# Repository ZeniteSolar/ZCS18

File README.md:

# ZCS18 - Zênite CAN! Shield 2018
The piece of hardware used in almost all modules in the boat of Zênite Solar Team on 2018.

## About

![zenite_logo] 

[Zênite Solar TEAM](https://github.com/ZeniteSolar) is an universitary project from [IFSC](http://www.ifsc.edu.br) focused on the development of a high performance solar boat for races and it aims to be completly open source.

- All the hardware was developed using [KiCad](http://kicad-pcb.org/);
- Simulations was done using [LTSpice](http://www.analog.com/en/design-center/design-tools-and-calculators/ltspice-simulator.html);
- Schematics are available [here][Schematic];
- BOM are available [here][BOM];

## Status

- [x] Simulations
- [x] Schematics
- [x] PCB
- [x] Fabrication
- [ ] Assembly
- [ ] Test
- [ ] Basic Firmware for reference

## Board View

![kicad3d_front_populated] 

***

[Schematic]: PDF/atmega_can_shield.pdf "Schematics"
[BOM]: PDF/BOM.pdf "Bill Of Materials"
[photo_front]: IMG/front.PNG "Fabricated Front"
[photo_back]: IMG/front.PNG "Fabricated Back"
[photo_front]: IMG/front.PNG "Populated Front"
[photo_back]: IMG/front.PNG "Populated Back"
[kicad3d_front]: IMG/front.PNG "Kicad Front"
[kicad3d_back]: IMG/back.PNG "Kicad Back"
[kicad3d_front_populated]: IMG/front_populated.PNG "Kicad Populated Front"
[kicad3d_back_populated]: IMG/back_populated.PNG "Kicad Populated Back"
[kicad3d_populated_angled]: IMG/populated_angled.PNG "Kicad Populated Board 3D View"
[zenite_logo]: https://avatars2.githubusercontent.com/u/8411347?s=100 "Zênite Solar Team Logo"

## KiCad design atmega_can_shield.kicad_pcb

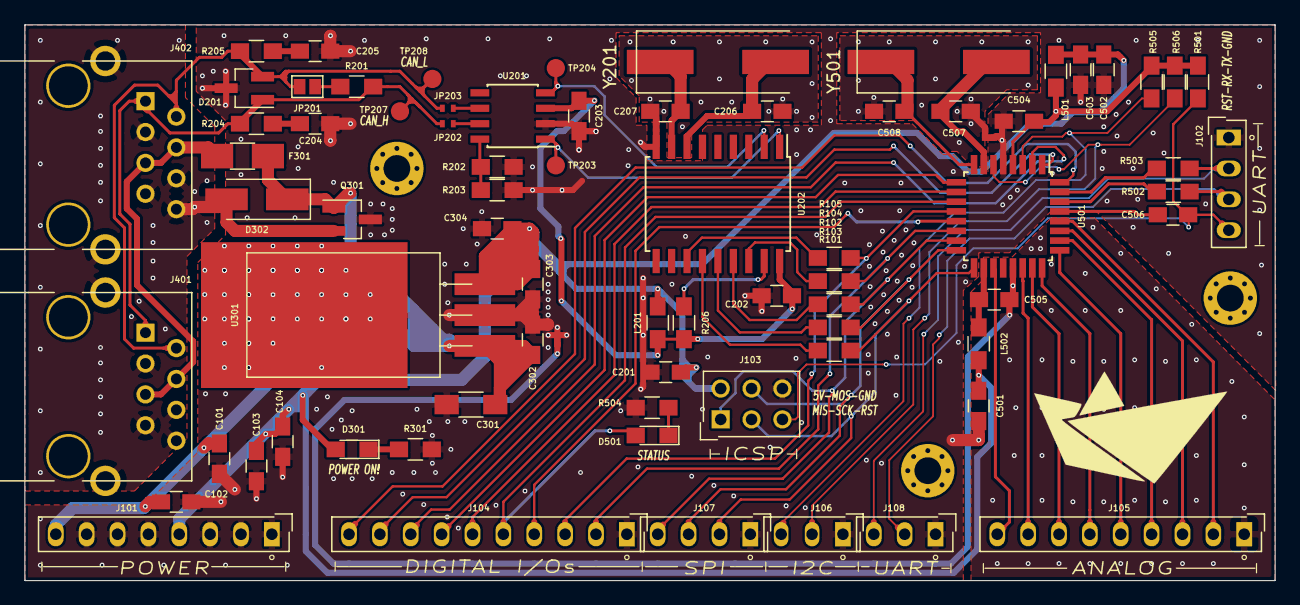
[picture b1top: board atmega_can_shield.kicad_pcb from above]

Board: 2 copper layers, 102.9 x 45.7 mm, 79 parts (0 on the bottom side), 60 nets.

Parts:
C101, C103, C503: 1u; C_0805_HandSoldering
C102, C104: 100n; C_0805_HandSoldering
C201, C202, C203, C302, C303, C501, C502, C504, C505, C506: 100nF; C_0805_HandSoldering
C204, C205: 560p; C_0805_HandSoldering
C206, C207, C507, C508: 22pF; C_0805_HandSoldering
C301: 10uF; C_1206_HandSoldering
C304: 1uF; C_0805_HandSoldering
D201: pesd1can; SOT-23_Handsoldering
D301, D501: LED_RED; LED_0805_HandSoldering
D302: TVS 24V 400W; D_SMA_Handsoldering
F301: 500mA resettable; Fuse_SMD1206_HandSoldering
J101: SUPPLY; SL-108-X-XX_1x08
J102: USART; SL-104-X-XX_1x04
J103: ICSP; SDL-106-X-XX_2x03
J104: DIGITAL I/Os; SL-110-X-XX_1x10
J105: ANALOG; SL-109-X-XX_1x09
J106: I2C; SL-103-X-XX_1x03
J107: SPI; SL-104-X-XX_1x04
J108: USART; SL-103-X-XX_1x03
J201, J301, J501: NetTie; µNetTie-I_Connected_SMD
J401, J402: RJ45; RJ45_YH59_01
JP201: Termination; GS2
JP202, JP203: Jumper_2_Open; R_0402_NoSilk
L201, L501, L502: 10uH; L_0805_HandSoldering
MK101, MK102, MK103: Mounting_Hole; MountingHole_2.2mm_M2_Pad_Via
Q301: si2308cds; SOT-23_Handsoldering
R101, R102, R103, R104, R105, R204, R205: 100; R_0805_HandSoldering
R201: 120; R_0805_HandSoldering
R202, R203, R206, R301, R501, R504, R505, R506: 10k; R_0805_HandSoldering
R502, R503: 1k; R_0805_HandSoldering
TP203: TXCAN; Measurement_Point_Round-SMD-Pad_Small
TP204: RXCAN; Measurement_Point_Round-SMD-Pad_Small
TP207: CAN_H; Measurement_Point_Round-SMD-Pad_Small
TP208: CAN_L; Measurement_Point_Round-SMD-Pad_Small
U201: MCP2551-I/SN; SOIC-8_3.9x4.9mm_Pitch1.27mm
U202: MCP2515-E/ST-SOIC18; SOIC-18W_7.5x11.6mm_Pitch1.27mm
U301: LM7805; TO-220_Horizontal_SMD
U501: ATMEGA328P-AU_alt; TQFP-32_7x7mm_Pitch0.8mm
Y201, Y501: 16MHz; Crystal_SMD_HC49_4HSMX

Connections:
+5V: C103.2, C104.1, C201.2, C303.1, C304.1, C501.1, C502.1, C503.2, D301.2, J101.4, J103.2, L201.2, L501.2, L502.2, U301.3
+5VA: C505.2, L502.1, U501.18
+5VD: C504.2, L501.1, R501.1, R505.1, R506.1, U501.4
+18V: C101.2, C102.1, C301.1, C302.1, D302.1, F301.2, J101.8, Q301.1, U301.1
/CANBUS CONN/CAN_GND: D302.2, J401.3, J401.6, J401.7, J401.8, J401.9, J402.3, J402.6, J402.7, J402.8, J402.9, Q301.2
/CANBUS CONN/CAN_H: D201.1, J401.1, J402.1, JP202.2, R201.2, R204.1, TP207.1
/CANBUS CONN/CAN_L: D201.2, J401.2, J402.2, JP201.2, JP203.2, R205.1, TP208.1
/CANBUS/CLK_N: C207.1, U202.8, Y201.1
/CANBUS/CLK_P: C206.2, U202.7, Y201.2
/CANBUS/CS: R104.1, U202.16
/CANBUS/INT: R105.1, U202.12
/CANBUS/RXCAN: TP204.1, U201.4, U202.2
/CANBUS/SCK: R101.1, U202.13
/CANBUS/SI: R103.1, U202.14
/CANBUS/SO: R102.1, U202.15
/CANBUS/TXCAN: TP203.1, U201.1, U202.1
/CANBUS/local_VCC: C202.2, C203.2, L201.1, R206.1, U201.3, U202.18
/MCU/ADC0: J105.7, U501.23
/MCU/ADC1: J105.6, U501.24
/MCU/ADC2: J105.5, U501.25
/MCU/ADC3: J105.4, U501.26
/MCU/ADC4: J105.3, U501.27
/MCU/ADC5: J105.2, U501.28
/MCU/ADC6: J105.9, U501.19
/MCU/ADC7: J105.8, U501.22
/MCU/CLK_N: C508.1, U501.8, Y501.1
/MCU/CLK_P: C507.1, U501.7, Y501.2
/MCU/MCP_INT: J104.3, R105.2, U501.12
/MCU/PB1: J104.4, U501.13
/MCU/PD2: J104.10, U501.32
/MCU/PD3: J104.9, U501.1
/MCU/PD4: J104.8, U501.2
/MCU/PD5: J104.7, U501.9
/MCU/PD6: J104.6, U501.10
/MCU/PD7: D501.2, J104.5, U501.11
/MCU/RST: C506.2, U501.29
/MCU/RX: R502.1, U501.30
/MCU/SCL1: J106.2, R506.2, U501.6
/MCU/SDA1: J106.3, R505.2, U501.3
/MCU/SPI_SS: J104.2, R104.2, U501.14
/MCU/TX: R503.1, U501.31
/MISO: J103.1, J107.4, R102.2, U501.15
/MOSI: J103.4, J107.3, R103.2, U501.16
/POWER SUPPLY/+18V_IN: F301.1, J401.4, J401.5, J402.4, J402.5
/RESET: C506.1, J102.4, J103.5, R501.2
/RX: J102.3, J108.2, R502.2
/SCK: J103.3, J107.2, R101.2, U501.17
/TX: J102.2, J108.3, R503.2
GND: C101.1, C102.2, C103.1, C104.2, C201.1, C202.1, C203.1, C204.1, C205.1, C301.2, C302.2, C303.2, C304.2, C501.2, C502.2, C503.1, C504.1, D201.3, J101.1, J101.2, J101.3, J101.5, J101.6, J101.7, J102.1, J103.6, J104.1, J106.1, J107.1, J108.1, J201.2, J301.1, J501.2, Q301.3, R202.2, R203.2, R301.2, R504.2, U201.2, U202.9, U301.2, U501.5
GNDA: C505.1, J105.1, J301.2, U501.21
GNDD: C206.1, C207.2, C507.2, C508.2, J201.1, J501.1
unnamed: C204.2, R204.2
unnamed: C205.2, R205.2
unnamed: D301.1, R301.1
unnamed: D501.1, R504.1
unnamed: JP201.1, R201.1
unnamed: JP202.1, U201.7
unnamed: JP203.1, U201.6
unnamed: R202.1, R203.1, U201.8
unnamed: R206.2, U202.17

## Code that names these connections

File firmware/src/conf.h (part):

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#define     BatOverVoltageInterrupt_PORT PORTD
#define     BatOverVoltageInterrupt_PIN  PIND
#define     BatOverVoltageInterrupt_DDR  DDRD
#define     BatOverVoltageInterrupt      PD2
#endif // ENABLE_HARDWARE_OVERVOLTAGE_INTERRUPT

#ifdef ENABLE_HARDWARE_ENABLE_SWITCH_INTERRUPT
#define     Enable_PORT             PORTD
#define     Enable_PIN              PIND
#define     Enable_DDR              DDRD
#define     Enable                  PD3
#endif // ENABLE_HARDWARE_ENABLE_SWITCH_INTERRUPT


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#define     PWM_PORT                PORTB
#define     PWM_PIN                 PINB
#define     PWM_DDR                 DDRB
#define     PWM                     PB1
#endif // PWM_ON

#ifdef LED_ON
#define     LED_PORT                PORTD
#define     LED_PIN                 PIND
#define     LED_DDR                 DDRD
#define     LED                     PD7
#define     cpl_led()               cpl_bit(LED_PORT, LED)
#define     set_led()               set_bit(LED_PORT, LED)
#define     clr_led()               clr_bit(LED_PORT, LED)
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
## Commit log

2018-05-26 First commit: the project was finished and mmanufactured (just the pcbs) but not tested nor documented yet.
2018-05-29 Changed 3D to KiCAD 5 and exported .wrl file
2018-05-29 PCB material changed to black on .wrl file.
2018-05-29 .step files changed to .wrl
2018-05-29 images was missing .PNG
2018-07-18 initial firmware copied from MCC17, small changes to compile and upload for 328pb
2018-07-18 changed MISO and MOSI using software serial
2018-07-18 added pragma messages for included modules
2018-07-20 Chaned to compile atmega328pb
2018-07-20 unecessary file.
2018-07-20 SILENCE enabled
2018-07-20 modules interdependency fixed
2018-07-20 gitignore updated
2018-07-20 Status led changed to new pin and added a blink pattern to main loop if MACHINE_ON isnt defined.
2018-07-20 ADC setted to 5kHz, some other minor improvements.
2018-07-20 Comments added
2018-07-20 USART, WATCHDOG, PWM, ADC working. Now testing machine
2018-07-20 ADC readings tested, ifdefs 8bits fixed
2018-07-20 ADC tested: OK. Reading 1021 at 5V, 0 at 0V
2018-07-22 PWM changed to mode 14 to get better resolution for 100kHz.
2018-07-22 code organization
2018-07-22 added a print version for 32 bits unsigned
2018-07-30 Added precompiled PWM configurations. Tested -> OK
2018-08-22 wdt time changed to 4 seconds because 2 wasn't fine
2018-08-22 This is almost the firmware for MCC module
2018-08-24 testing...
2018-08-24 adc_data_ready changed to machine_run instead task_running to ensure that moving average is rightly done
2018-08-24 adc_data_ready initialized in adc_init instead adc.h
2018-08-24 algorithm for zero power detection enhanced
2018-08-25 checks are now part of a decision tree centralized inside read_and_check_adcs(void)
2018-08-25 machine prints was causing clock conflict. Fixed
2018-08-25 remove duplicated F_CPU define
2018-08-26 various specific changes
2018-08-26 doc added
2018-08-26 simple average added.
2018-08-27 last test night codes. adc avg was fixed, and peo was tested but not correctly working yet
2018-08-31 adc linearized to mV and mA with good precision, and ERROR detection was implemented, but not fully tested yet.
2018-09-02 clean up old functions
2018-09-02 organized to work with several configurations, aka sweep, p&o or just a fixed PWM
2018-09-02 minor changes to test the power converter without checks and algorithms.
2018-09-02 added a cpp check option
2018-09-04 ADC frequency is now configured at conf.h. ADC frequency was scaled up to 10khz working.
2018-09-04 multiplications for adc conversion was fixed by especifying the data types.
2018-09-04 sweep don't need to be inline.
2018-09-05 algorithms fixed. every combination of configuration are OK (tested)
2018-09-06 small fixes
2018-09-06 input power and battery voltage software limitations included. Battery Voltage limitations was tested under simulated conditions (using 12V battery and DC power supply).
2018-09-06 small fixes for ifdefs logic
2018-09-06 hardware battery overvoltage protection configured and tested just FINE.
2018-09-06 clean up
2018-09-06 added pi max config print
2018-09-06 FAKE_ADC config added test logic without the power converter
2018-09-08 bootload burner script added
2018-09-08 compiling again for 328p
2018-09-10 config to test before buzios
